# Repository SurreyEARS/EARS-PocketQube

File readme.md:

The SurreyEARS foray into picosatellite development. We are using the new PQ60 V1.1 Standard from  http://pqinfo.info

See the project wiki here: http://wiki.surreyears.co.uk/index.php/EARS_PocketQube_Picosatellite

License
=======

EARS-Pocketqube | http://wiki.surreyears.co.uk/index.php/EARS_PocketQube_Picosatellite
Copyright (c) 2015 SurreyEARS

This is an open hardware design licensed under the terms of the CERN Open
Hardware Licence (OHL) v1.2.

You may redistribute and modify this documentation under the terms of the CERN
OHL v.1.2 (http://ohwr.org/cernohl). This documentation is distributed WITHOUT
ANY EXPRESS OR IMPLIED WARRANTY, INCLUDING OF MERCHANTABILITY, SATISFACTORY
QUALITY AND FITNESS FOR A PARTICULAR PURPOSE. Please see the CERN OHL v.1.2 for
applicable conditions.

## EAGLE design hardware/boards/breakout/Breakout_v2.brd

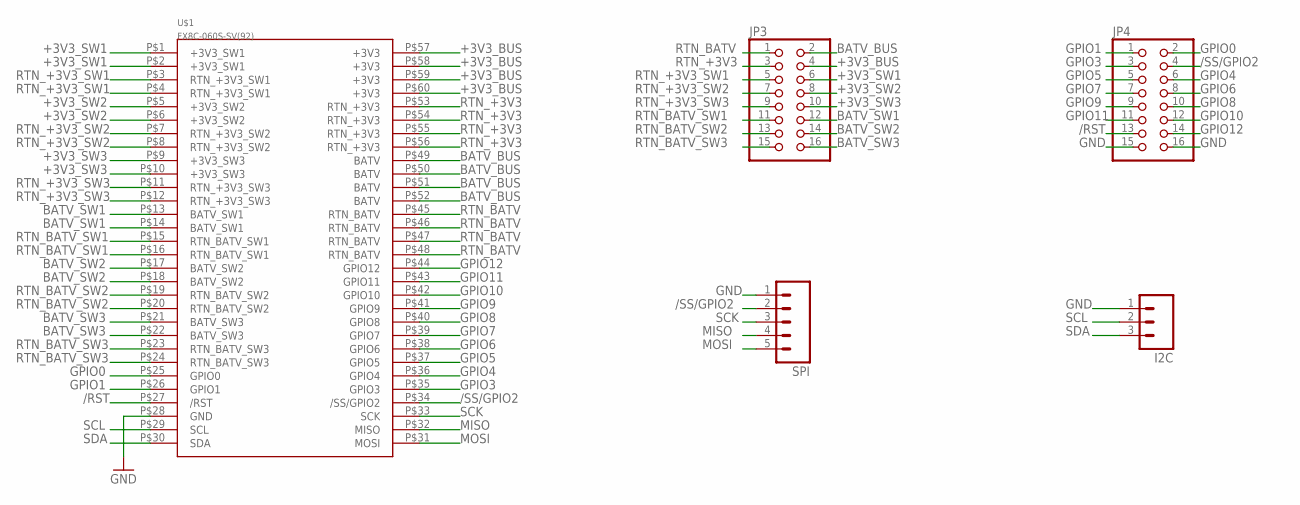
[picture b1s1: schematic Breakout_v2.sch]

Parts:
I2C: M03PTH; 1X03
JP3, JP4: PINHD-2X8; 2X08
SPI: M05PTH; 1X05
U$1: FX8C-060S-SV(92)

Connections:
+3V3_BUS: JP3.4, U$1.P$57 (+3V3), U$1.P$58 (+3V3), U$1.P$59 (+3V3), U$1.P$60 (+3V3)
+3V3_SW1: JP3.6, U$1.P$1 (+3V3_SW1), U$1.P$2 (+3V3_SW1)
+3V3_SW2: JP3.8, U$1.P$5 (+3V3_SW2), U$1.P$6 (+3V3_SW2)
+3V3_SW3: JP3.10, U$1.P$9 (+3V3_SW3), U$1.P$10 (+3V3_SW3)
/RST: JP4.13, U$1.P$27 (/RST)
/SS/GPIO2: JP4.4, SPI.2, U$1.P$34 (/SS/GPIO2)
BATV_BUS: JP3.2, U$1.P$49 (BATV), U$1.P$50 (BATV), U$1.P$51 (BATV), U$1.P$52 (BATV)
BATV_SW1: JP3.12, U$1.P$13 (BATV_SW1), U$1.P$14 (BATV_SW1)
BATV_SW2: JP3.14, U$1.P$17 (BATV_SW2), U$1.P$18 (BATV_SW2)
BATV_SW3: JP3.16, U$1.P$21 (BATV_SW3), U$1.P$22 (BATV_SW3)
GND: I2C.1, JP4.15, JP4.16, SPI.1, U$1.P$28 (GND)
GPIO0: JP4.2, U$1.P$25 (GPIO0)
GPIO1: JP4.1, U$1.P$26 (GPIO1)
GPIO3: JP4.3, U$1.P$35 (GPIO3)
GPIO4: JP4.6, U$1.P$36 (GPIO4)
GPIO5: JP4.5, U$1.P$37 (GPIO5)
GPIO6: JP4.8, U$1.P$38 (GPIO6)
GPIO7: JP4.7, U$1.P$39 (GPIO7)
GPIO8: JP4.10, U$1.P$40 (GPIO8)
GPIO9: JP4.9, U$1.P$41 (GPIO9)
GPIO10: JP4.12, U$1.P$42 (GPIO10)
GPIO11: JP4.11, U$1.P$43 (GPIO11)
GPIO12: JP4.14, U$1.P$44 (GPIO12)
MISO: SPI.4, U$1.P$32 (MISO)
MOSI: SPI.5, U$1.P$31 (MOSI)
RTN_+3V3: JP3.3, U$1.P$53 (RTN_+3V3), U$1.P$54 (RTN_+3V3), U$1.P$55 (RTN_+3V3), U$1.P$56 (RTN_+3V3)
RTN_+3V3_SW1: JP3.5, U$1.P$3 (RTN_+3V3_SW1), U$1.P$4 (RTN_+3V3_SW1)
RTN_+3V3_SW2: JP3.7, U$1.P$7 (RTN_+3V3_SW2), U$1.P$8 (RTN_+3V3_SW2)
RTN_+3V3_SW3: JP3.9, U$1.P$11 (RTN_+3V3_SW3), U$1.P$12 (RTN_+3V3_SW3)
RTN_BATV: JP3.1, U$1.P$45 (RTN_BATV), U$1.P$46 (RTN_BATV), U$1.P$47 (RTN_BATV), U$1.P$48 (RTN_BATV)
RTN_BATV_SW1: JP3.11, U$1.P$15 (RTN_BATV_SW1), U$1.P$16 (RTN_BATV_SW1)
RTN_BATV_SW2: JP3.13, U$1.P$19 (RTN_BATV_SW2), U$1.P$20 (RTN_BATV_SW2)
RTN_BATV_SW3: JP3.15, U$1.P$23 (RTN_BATV_SW3), U$1.P$24 (RTN_BATV_SW3)
SCK: SPI.3, U$1.P$33 (SCK)
SCL: I2C.2, U$1.P$29 (SCL)
SDA: I2C.3, U$1.P$30 (SDA)

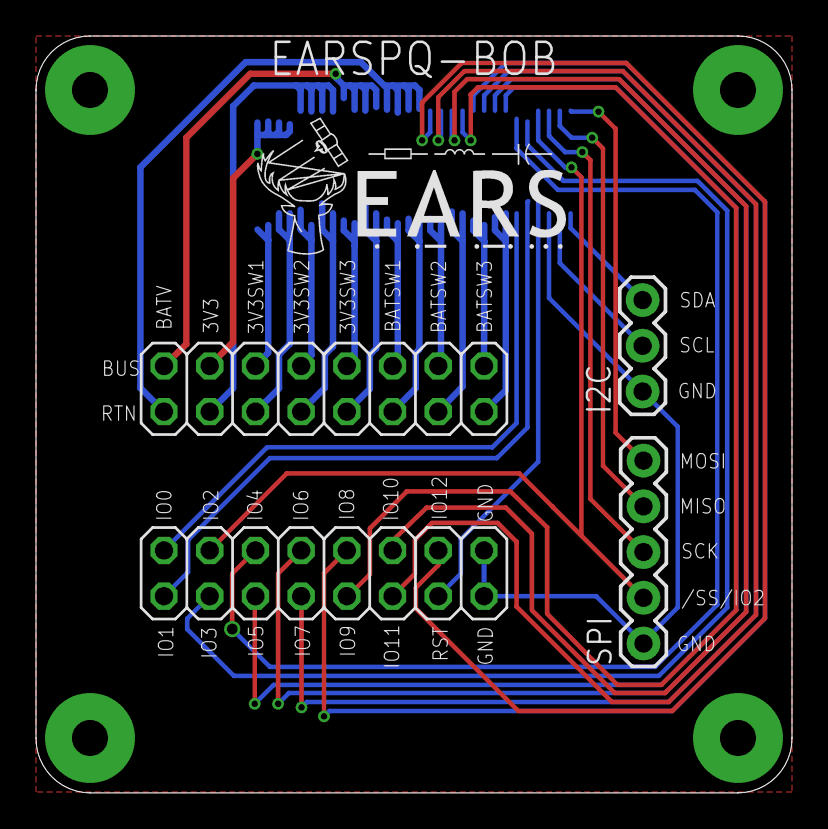
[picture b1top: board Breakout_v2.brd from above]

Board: 2 copper layers, 42.0 x 42.0 mm, 6 parts (1 on the bottom side), 36 nets.

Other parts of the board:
U$2: EARSLOGOFULL

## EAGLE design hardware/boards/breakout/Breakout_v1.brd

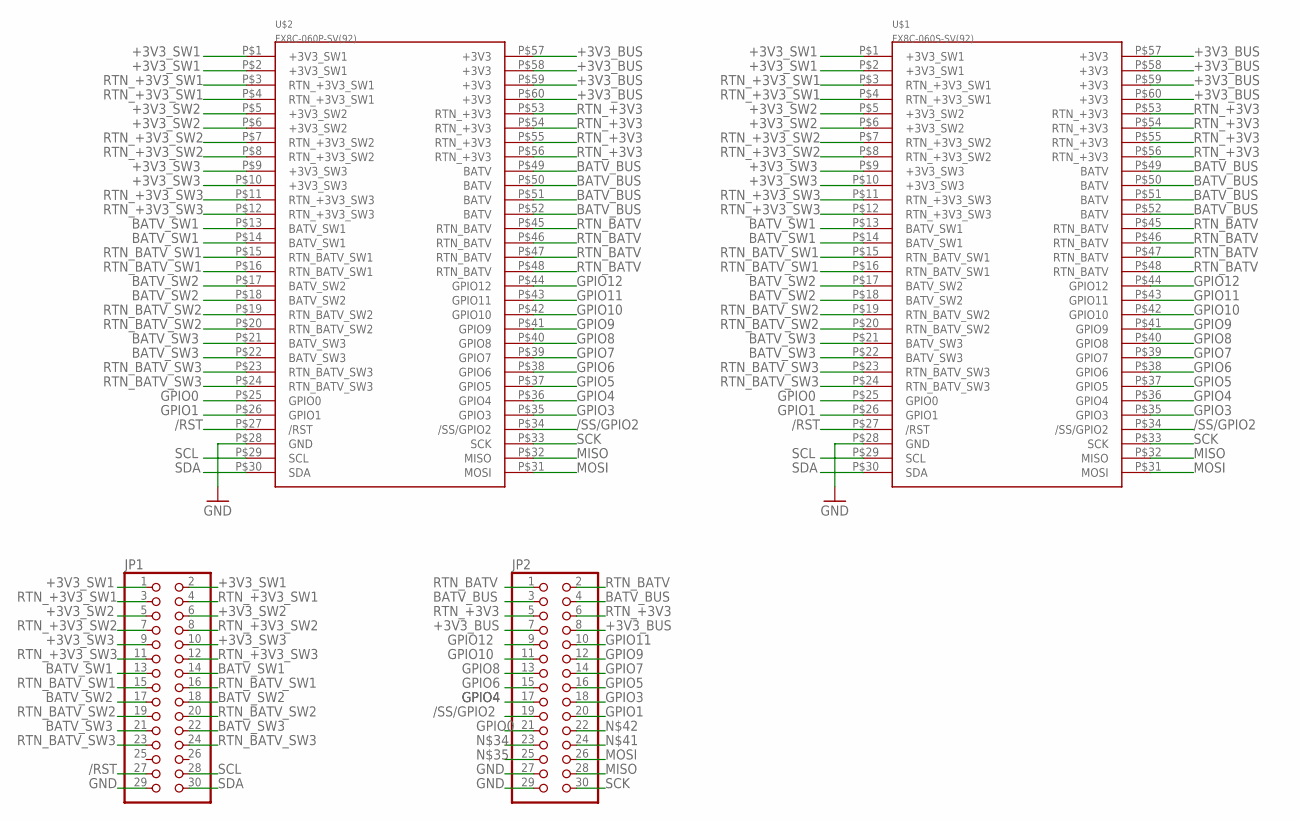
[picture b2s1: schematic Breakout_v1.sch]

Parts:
JP1, JP2: PINHD-2X15; 2X15
U$1: FX8C-060S-SV(92)
U$2: FX8C-060P-SV(92)

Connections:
+3V3_BUS: JP2.7, JP2.8, U$1.P$57 (+3V3), U$1.P$58 (+3V3), U$1.P$59 (+3V3), U$1.P$60 (+3V3), U$2.P$57 (+3V3), U$2.P$58 (+3V3), U$2.P$59 (+3V3), U$2.P$60 (+3V3)
+3V3_SW1: JP1.1, JP1.2, U$1.P$1 (+3V3_SW1), U$1.P$2 (+3V3_SW1), U$2.P$1 (+3V3_SW1), U$2.P$2 (+3V3_SW1)
+3V3_SW2: JP1.5, JP1.6, U$1.P$5 (+3V3_SW2), U$1.P$6 (+3V3_SW2), U$2.P$5 (+3V3_SW2), U$2.P$6 (+3V3_SW2)
+3V3_SW3: JP1.9, JP1.10, U$1.P$9 (+3V3_SW3), U$1.P$10 (+3V3_SW3), U$2.P$9 (+3V3_SW3), U$2.P$10 (+3V3_SW3)
/RST: JP1.27, U$1.P$27 (/RST), U$2.P$27 (/RST)
/SS/GPIO2: JP2.19, U$1.P$34 (/SS/GPIO2), U$2.P$34 (/SS/GPIO2)
BATV_BUS: JP2.3, JP2.4, U$1.P$49 (BATV), U$1.P$50 (BATV), U$1.P$51 (BATV), U$1.P$52 (BATV), U$2.P$49 (BATV), U$2.P$50 (BATV), U$2.P$51 (BATV), U$2.P$52 (BATV)
BATV_SW1: JP1.13, JP1.14, U$1.P$13 (BATV_SW1), U$1.P$14 (BATV_SW1), U$2.P$13 (BATV_SW1), U$2.P$14 (BATV_SW1)
BATV_SW2: JP1.17, JP1.18, U$1.P$17 (BATV_SW2), U$1.P$18 (BATV_SW2), U$2.P$17 (BATV_SW2), U$2.P$18 (BATV_SW2)
BATV_SW3: JP1.21, JP1.22, U$1.P$21 (BATV_SW3), U$1.P$22 (BATV_SW3), U$2.P$21 (BATV_SW3), U$2.P$22 (BATV_SW3)
GND: JP1.29, JP2.27, JP2.29, U$1.P$28 (GND), U$2.P$28 (GND)
GPIO0: JP2.21, U$1.P$25 (GPIO0), U$2.P$25 (GPIO0)
GPIO1: JP2.20, U$1.P$26 (GPIO1), U$2.P$26 (GPIO1)
GPIO3: JP2.18, U$1.P$35 (GPIO3), U$2.P$35 (GPIO3)
GPIO4: JP2.17, U$1.P$36 (GPIO4), U$2.P$36 (GPIO4)
GPIO5: JP2.16, U$1.P$37 (GPIO5), U$2.P$37 (GPIO5)
GPIO6: JP2.15, U$1.P$38 (GPIO6), U$2.P$38 (GPIO6)
GPIO7: JP2.14, U$1.P$39 (GPIO7), U$2.P$39 (GPIO7)
GPIO8: JP2.13, U$1.P$40 (GPIO8), U$2.P$40 (GPIO8)
GPIO9: JP2.12, U$1.P$41 (GPIO9), U$2.P$41 (GPIO9)
GPIO10: JP2.11, U$1.P$42 (GPIO10), U$2.P$42 (GPIO10)
GPIO11: JP2.10, U$1.P$43 (GPIO11), U$2.P$43 (GPIO11)
GPIO12: JP2.9, U$1.P$44 (GPIO12), U$2.P$44 (GPIO12)
MISO: JP2.28, U$1.P$32 (MISO), U$2.P$32 (MISO)
MOSI: JP2.26, U$1.P$31 (MOSI), U$2.P$31 (MOSI)
RTN_+3V3: JP2.5, JP2.6, U$1.P$53 (RTN_+3V3), U$1.P$54 (RTN_+3V3), U$1.P$55 (RTN_+3V3), U$1.P$56 (RTN_+3V3), U$2.P$53 (RTN_+3V3), U$2.P$54 (RTN_+3V3), U$2.P$55 (RTN_+3V3), U$2.P$56 (RTN_+3V3)
RTN_+3V3_SW1: JP1.3, JP1.4, U$1.P$3 (RTN_+3V3_SW1), U$1.P$4 (RTN_+3V3_SW1), U$2.P$3 (RTN_+3V3_SW1), U$2.P$4 (RTN_+3V3_SW1)
RTN_+3V3_SW2: JP1.7, JP1.8, U$1.P$7 (RTN_+3V3_SW2), U$1.P$8 (RTN_+3V3_SW2), U$2.P$7 (RTN_+3V3_SW2), U$2.P$8 (RTN_+3V3_SW2)
RTN_+3V3_SW3: JP1.11, JP1.12, U$1.P$11 (RTN_+3V3_SW3), U$1.P$12 (RTN_+3V3_SW3), U$2.P$11 (RTN_+3V3_SW3), U$2.P$12 (RTN_+3V3_SW3)
RTN_BATV: JP2.1, JP2.2, U$1.P$45 (RTN_BATV), U$1.P$46 (RTN_BATV), U$1.P$47 (RTN_BATV), U$1.P$48 (RTN_BATV), U$2.P$45 (RTN_BATV), U$2.P$46 (RTN_BATV), U$2.P$47 (RTN_BATV), U$2.P$48 (RTN_BATV)
RTN_BATV_SW1: JP1.15, JP1.16, U$1.P$15 (RTN_BATV_SW1), U$1.P$16 (RTN_BATV_SW1), U$2.P$15 (RTN_BATV_SW1), U$2.P$16 (RTN_BATV_SW1)
RTN_BATV_SW2: JP1.19, JP1.20, U$1.P$19 (RTN_BATV_SW2), U$1.P$20 (RTN_BATV_SW2), U$2.P$19 (RTN_BATV_SW2), U$2.P$20 (RTN_BATV_SW2)
RTN_BATV_SW3: JP1.23, JP1.24, U$1.P$23 (RTN_BATV_SW3), U$1.P$24 (RTN_BATV_SW3), U$2.P$23 (RTN_BATV_SW3), U$2.P$24 (RTN_BATV_SW3)
SCK: JP2.30, U$1.P$33 (SCK), U$2.P$33 (SCK)
SCL: JP1.28, U$1.P$29 (SCL), U$2.P$29 (SCL)
SDA: JP1.30, U$1.P$30 (SDA), U$2.P$30 (SDA)

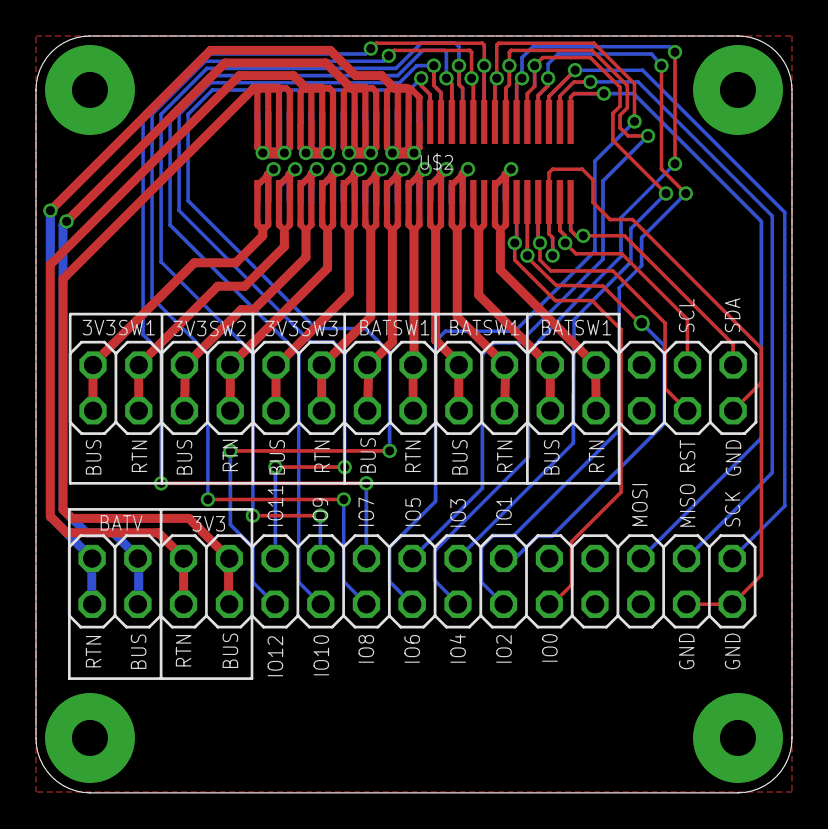
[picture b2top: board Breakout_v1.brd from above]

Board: 2 copper layers, 42.0 x 42.0 mm, 4 parts (1 on the bottom side), 36 nets.

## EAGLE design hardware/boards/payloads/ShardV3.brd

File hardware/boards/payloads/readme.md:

This folder will contain designs for payload boards. Current ideas include:

* Camera
* Radiation Detection
* Prototyping

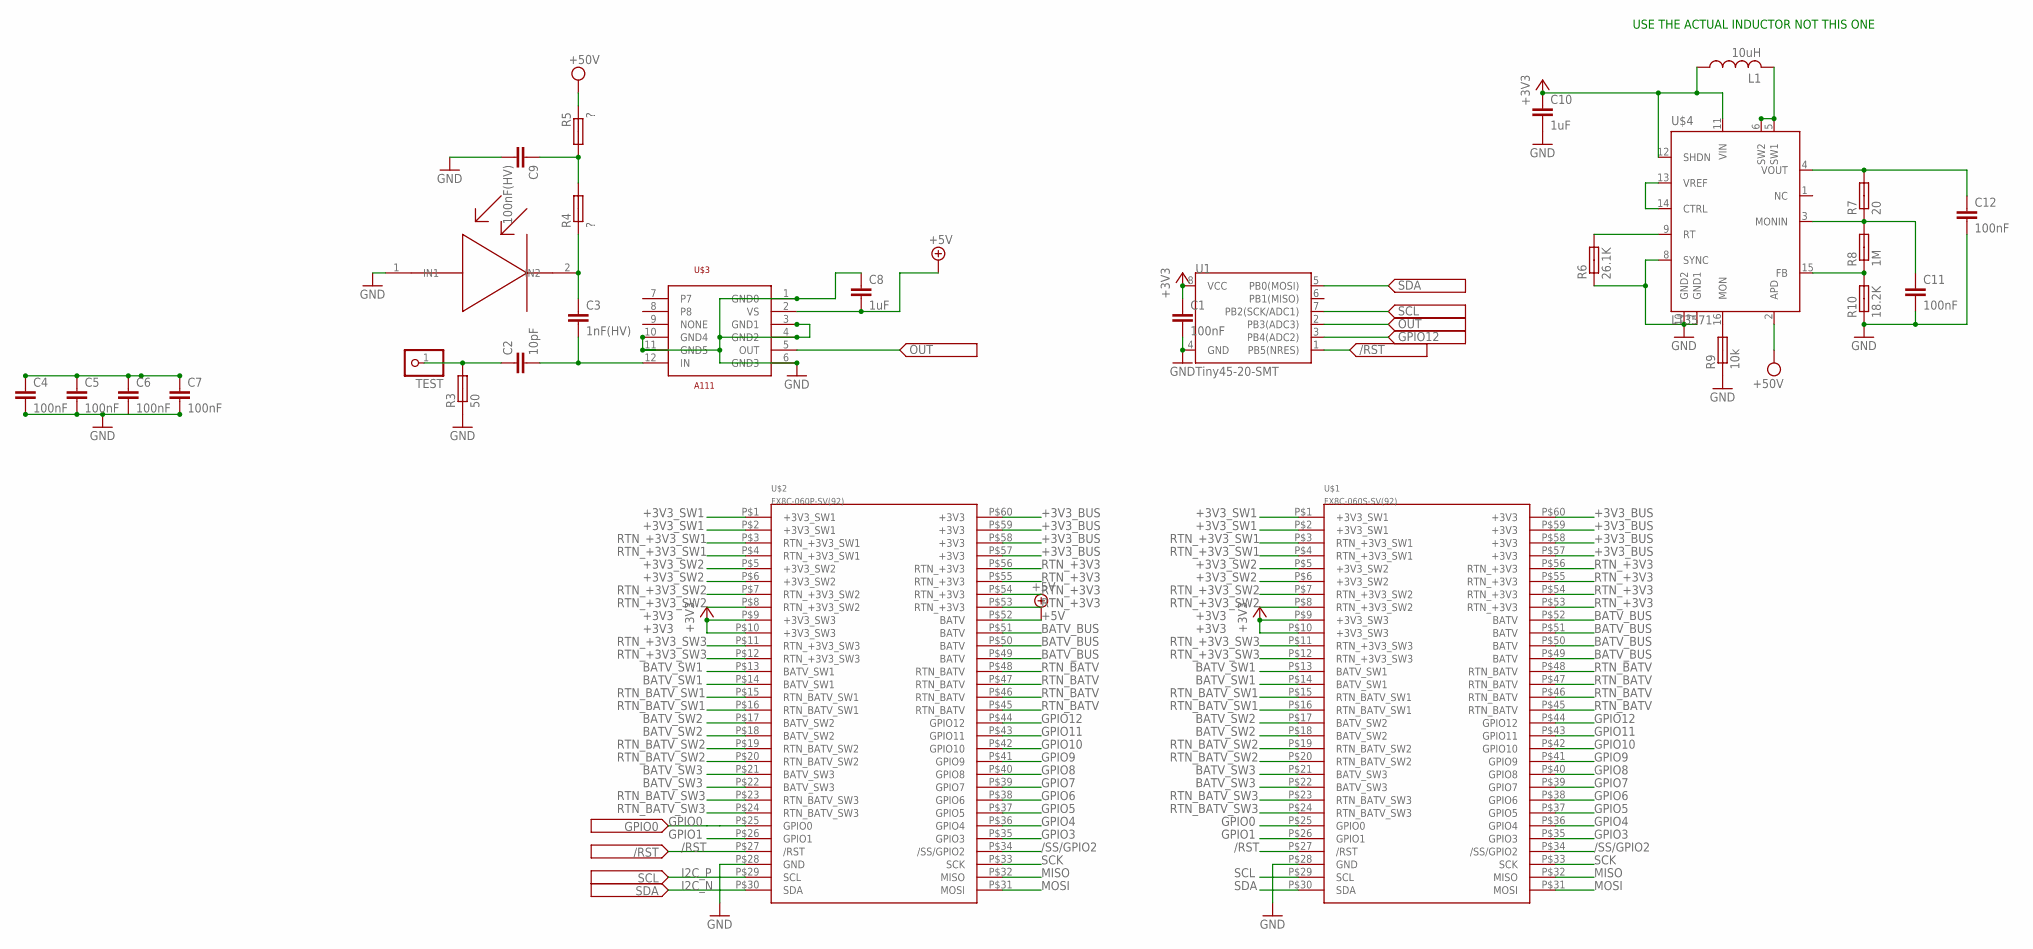
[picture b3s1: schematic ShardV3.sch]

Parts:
C1, C4, C5, C6, C7: 100nF; C0402
C2: 10pF; C0402
C3: 1nF(HV); C0603
C8, C10: 1uF; C0603
C9: 100nF(HV); C0603
C11, C12: 100nF; C0603
L1: 10uH; L1812
NDD: S3590-08
R3: 50; R0402
R4, R5: ?; R0402
R6: 26.1K; R0402
R7: 20; R0402
R8: 1M; R0402
R9: 10k; R0402
R10: 18.2K; R0402
TEST: PINHD-1X1; 1X01
U1: Tiny45-20-SMT; SO08-EIAJ
U$1: FX8C-060S-SV(92)
U$2: FX8C-060P-SV(92)
U$3: A111CHIP
U$4: LT3571; QFN3X3-6

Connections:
+3V3: C1.1, C10.1, L1.1, U1.8 (VCC), U$1.P$9 (+3V3_SW3), U$1.P$10 (+3V3_SW3), U$2.P$9 (+3V3_SW3), U$2.P$10 (+3V3_SW3), U$4.11 (VIN), U$4.12 (SHDN)
+3V3_BUS: U$1.P$57 (+3V3), U$1.P$58 (+3V3), U$1.P$59 (+3V3), U$1.P$60 (+3V3), U$2.P$57 (+3V3), U$2.P$58 (+3V3), U$2.P$59 (+3V3), U$2.P$60 (+3V3)
+3V3_SW1: U$1.P$1 (+3V3_SW1), U$1.P$2 (+3V3_SW1), U$2.P$1 (+3V3_SW1), U$2.P$2 (+3V3_SW1)
+3V3_SW2: U$1.P$5 (+3V3_SW2), U$1.P$6 (+3V3_SW2), U$2.P$5 (+3V3_SW2), U$2.P$6 (+3V3_SW2)
+5V: C8.2, U$2.P$52 (BATV), U$3.2 (VS)
/RST: U1.1 (PB5(NRES)), U$1.P$27 (/RST), U$2.P$27 (/RST)
/SS/GPIO2: U$1.P$34 (/SS/GPIO2), U$2.P$34 (/SS/GPIO2)
BATV_BUS: U$1.P$49 (BATV), U$1.P$50 (BATV), U$1.P$51 (BATV), U$1.P$52 (BATV), U$2.P$49 (BATV), U$2.P$50 (BATV), U$2.P$51 (BATV)
BATV_SW1: U$1.P$13 (BATV_SW1), U$1.P$14 (BATV_SW1), U$2.P$13 (BATV_SW1), U$2.P$14 (BATV_SW1)
BATV_SW2: U$1.P$17 (BATV_SW2), U$1.P$18 (BATV_SW2), U$2.P$17 (BATV_SW2), U$2.P$18 (BATV_SW2)
BATV_SW3: U$1.P$21 (BATV_SW3), U$1.P$22 (BATV_SW3), U$2.P$21 (BATV_SW3), U$2.P$22 (BATV_SW3)
CHASSIS_GND: C4.1, C5.1, C6.1, C7.1
GND: C1.2, C4.2, C5.2, C7.2, C8.1, C9.2, C10.2, C11.2, C12.2, NDD.1 (IN1), R3.1, R6.1, R9.1, R10.1, U1.4 (GND), U$1.P$28 (GND), U$2.P$28 (GND), U$3.1 (GND0), U$3.3 (GND1), U$3.4 (GND2), U$3.6 (GND3), U$3.10 (GND4), U$3.11 (GND5), U$4.7 (GND1), U$4.8 (SYNC), U$4.10 (GND2)
GPIO0: U$1.P$25 (GPIO0), U$2.P$25 (GPIO0)
GPIO1: U$1.P$26 (GPIO1), U$2.P$26 (GPIO1)
GPIO3: U$1.P$35 (GPIO3), U$2.P$35 (GPIO3)
GPIO4: U$1.P$36 (GPIO4), U$2.P$36 (GPIO4)
GPIO5: U$1.P$37 (GPIO5), U$2.P$37 (GPIO5)
GPIO6: U$1.P$38 (GPIO6), U$2.P$38 (GPIO6)
GPIO7: U$1.P$39 (GPIO7), U$2.P$39 (GPIO7)
GPIO8: U$1.P$40 (GPIO8), U$2.P$40 (GPIO8)
GPIO9: U$1.P$41 (GPIO9), U$2.P$41 (GPIO9)
GPIO10: U$1.P$42 (GPIO10), U$2.P$42 (GPIO10)
GPIO11: U$1.P$43 (GPIO11), U$2.P$43 (GPIO11)
GPIO12: U1.3 (PB4(ADC2)), U$1.P$44 (GPIO12), U$2.P$44 (GPIO12)
I2C_N: U1.5 (PB0(MOSI)), U$2.P$30 (SDA)
I2C_P: U1.7 (PB2(SCK/ADC1)), U$2.P$29 (SCL)
MISO: U$1.P$32 (MISO), U$2.P$32 (MISO)
MOSI: U$1.P$31 (MOSI), U$2.P$31 (MOSI)
unnamed: C2.1, R3.2, TEST.1
unnamed: C2.2, C3.2, U$3.12 (IN)
unnamed: C3.1, NDD.2 (IN2), R4.1
unnamed: L1.2, U$4.5 (SW1), U$4.6 (SW2)
unnamed: C9.1, R4.2, R5.2
unnamed: U$4.13 (VREF), U$4.14 (CTRL)
unnamed: R6.2, U$4.9 (RT)
unnamed: C11.1, R7.1, R8.2, U$4.3 (MONIN)
unnamed: C12.1, R7.2, U$4.4 (VOUT)
unnamed: R8.1, R10.2, U$4.15 (FB)
unnamed: R9.2, U$4.16 (MON)
OUT: U1.2 (PB3(ADC3)), U$3.5 (OUT)
RTN_+3V3: U$1.P$53 (RTN_+3V3), U$1.P$54 (RTN_+3V3), U$1.P$55 (RTN_+3V3), U$1.P$56 (RTN_+3V3), U$2.P$53 (RTN_+3V3), U$2.P$54 (RTN_+3V3), U$2.P$55 (RTN_+3V3), U$2.P$56 (RTN_+3V3)
RTN_+3V3_SW1: U$1.P$3 (RTN_+3V3_SW1), U$1.P$4 (RTN_+3V3_SW1), U$2.P$3 (RTN_+3V3_SW1), U$2.P$4 (RTN_+3V3_SW1)
RTN_+3V3_SW2: U$1.P$7 (RTN_+3V3_SW2), U$1.P$8 (RTN_+3V3_SW2), U$2.P$7 (RTN_+3V3_SW2), U$2.P$8 (RTN_+3V3_SW2)
RTN_+3V3_SW3: U$1.P$11 (RTN_+3V3_SW3), U$1.P$12 (RTN_+3V3_SW3), U$2.P$11 (RTN_+3V3_SW3), U$2.P$12 (RTN_+3V3_SW3)
RTN_BATV: U$1.P$45 (RTN_BATV), U$1.P$46 (RTN_BATV), U$1.P$47 (RTN_BATV), U$1.P$48 (RTN_BATV), U$2.P$45 (RTN_BATV), U$2.P$46 (RTN_BATV), U$2.P$47 (RTN_BATV), U$2.P$48 (RTN_BATV)
RTN_BATV_SW1: U$1.P$15 (RTN_BATV_SW1), U$1.P$16 (RTN_BATV_SW1), U$2.P$15 (RTN_BATV_SW1), U$2.P$16 (RTN_BATV_SW1)
RTN_BATV_SW2: U$1.P$19 (RTN_BATV_SW2), U$1.P$20 (RTN_BATV_SW2), U$2.P$19 (RTN_BATV_SW2), U$2.P$20 (RTN_BATV_SW2)
RTN_BATV_SW3: U$1.P$23 (RTN_BATV_SW3), U$1.P$24 (RTN_BATV_SW3), U$2.P$23 (RTN_BATV_SW3), U$2.P$24 (RTN_BATV_SW3)
SCK: U$1.P$33 (SCK), U$2.P$33 (SCK)
SCL: U$1.P$29 (SCL)
SDA: U$1.P$30 (SDA)
VPP: R5.1, U$4.2 (APD)

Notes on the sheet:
USE THE ACTUAL INDUCTOR NOT THIS ONE

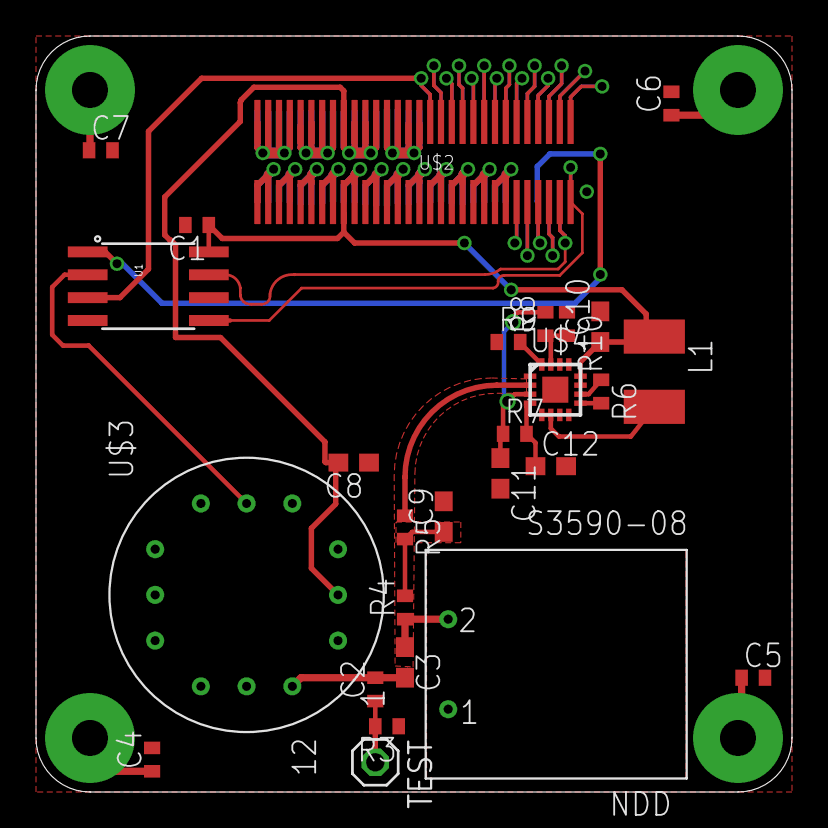
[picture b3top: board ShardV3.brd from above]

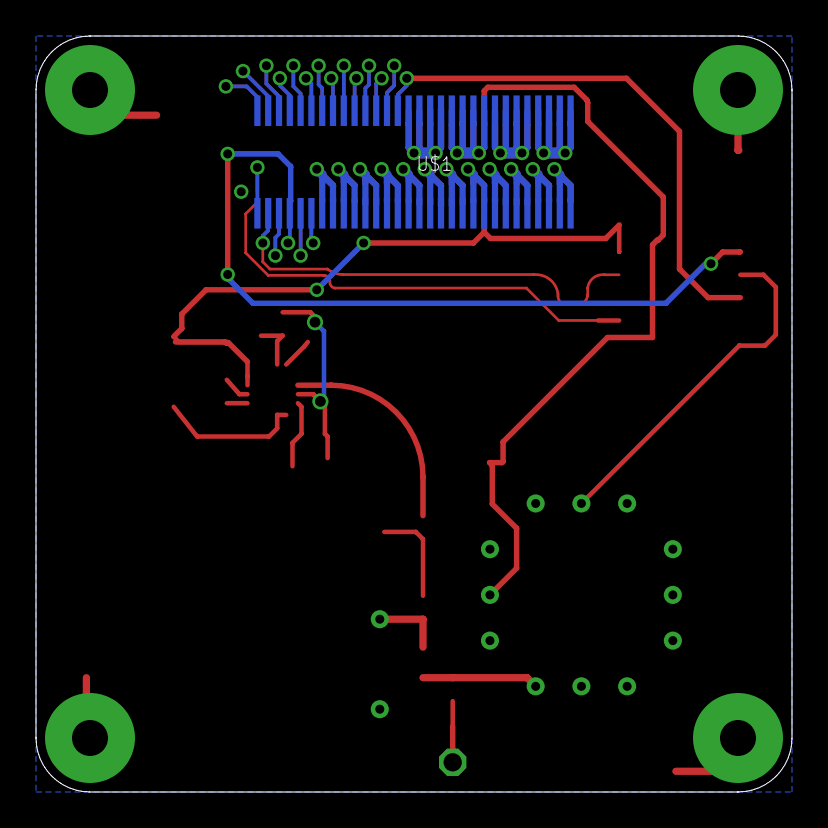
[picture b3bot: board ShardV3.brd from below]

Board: 2 copper layers, 42.0 x 42.0 mm, 29 parts (2 on the bottom side), 51 nets.

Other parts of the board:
U$5: EARSLOGOFULL

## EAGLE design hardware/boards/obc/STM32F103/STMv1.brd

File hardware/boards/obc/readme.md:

We are intending to roll out several obc boards which contain different processors.

Current ideas include:
* ATMega328P
* Teensy (ARM Cortex M4)
* STM Nucleo
* TI MSP430
* Freescale Kinetis L
* Intel Edison(!)

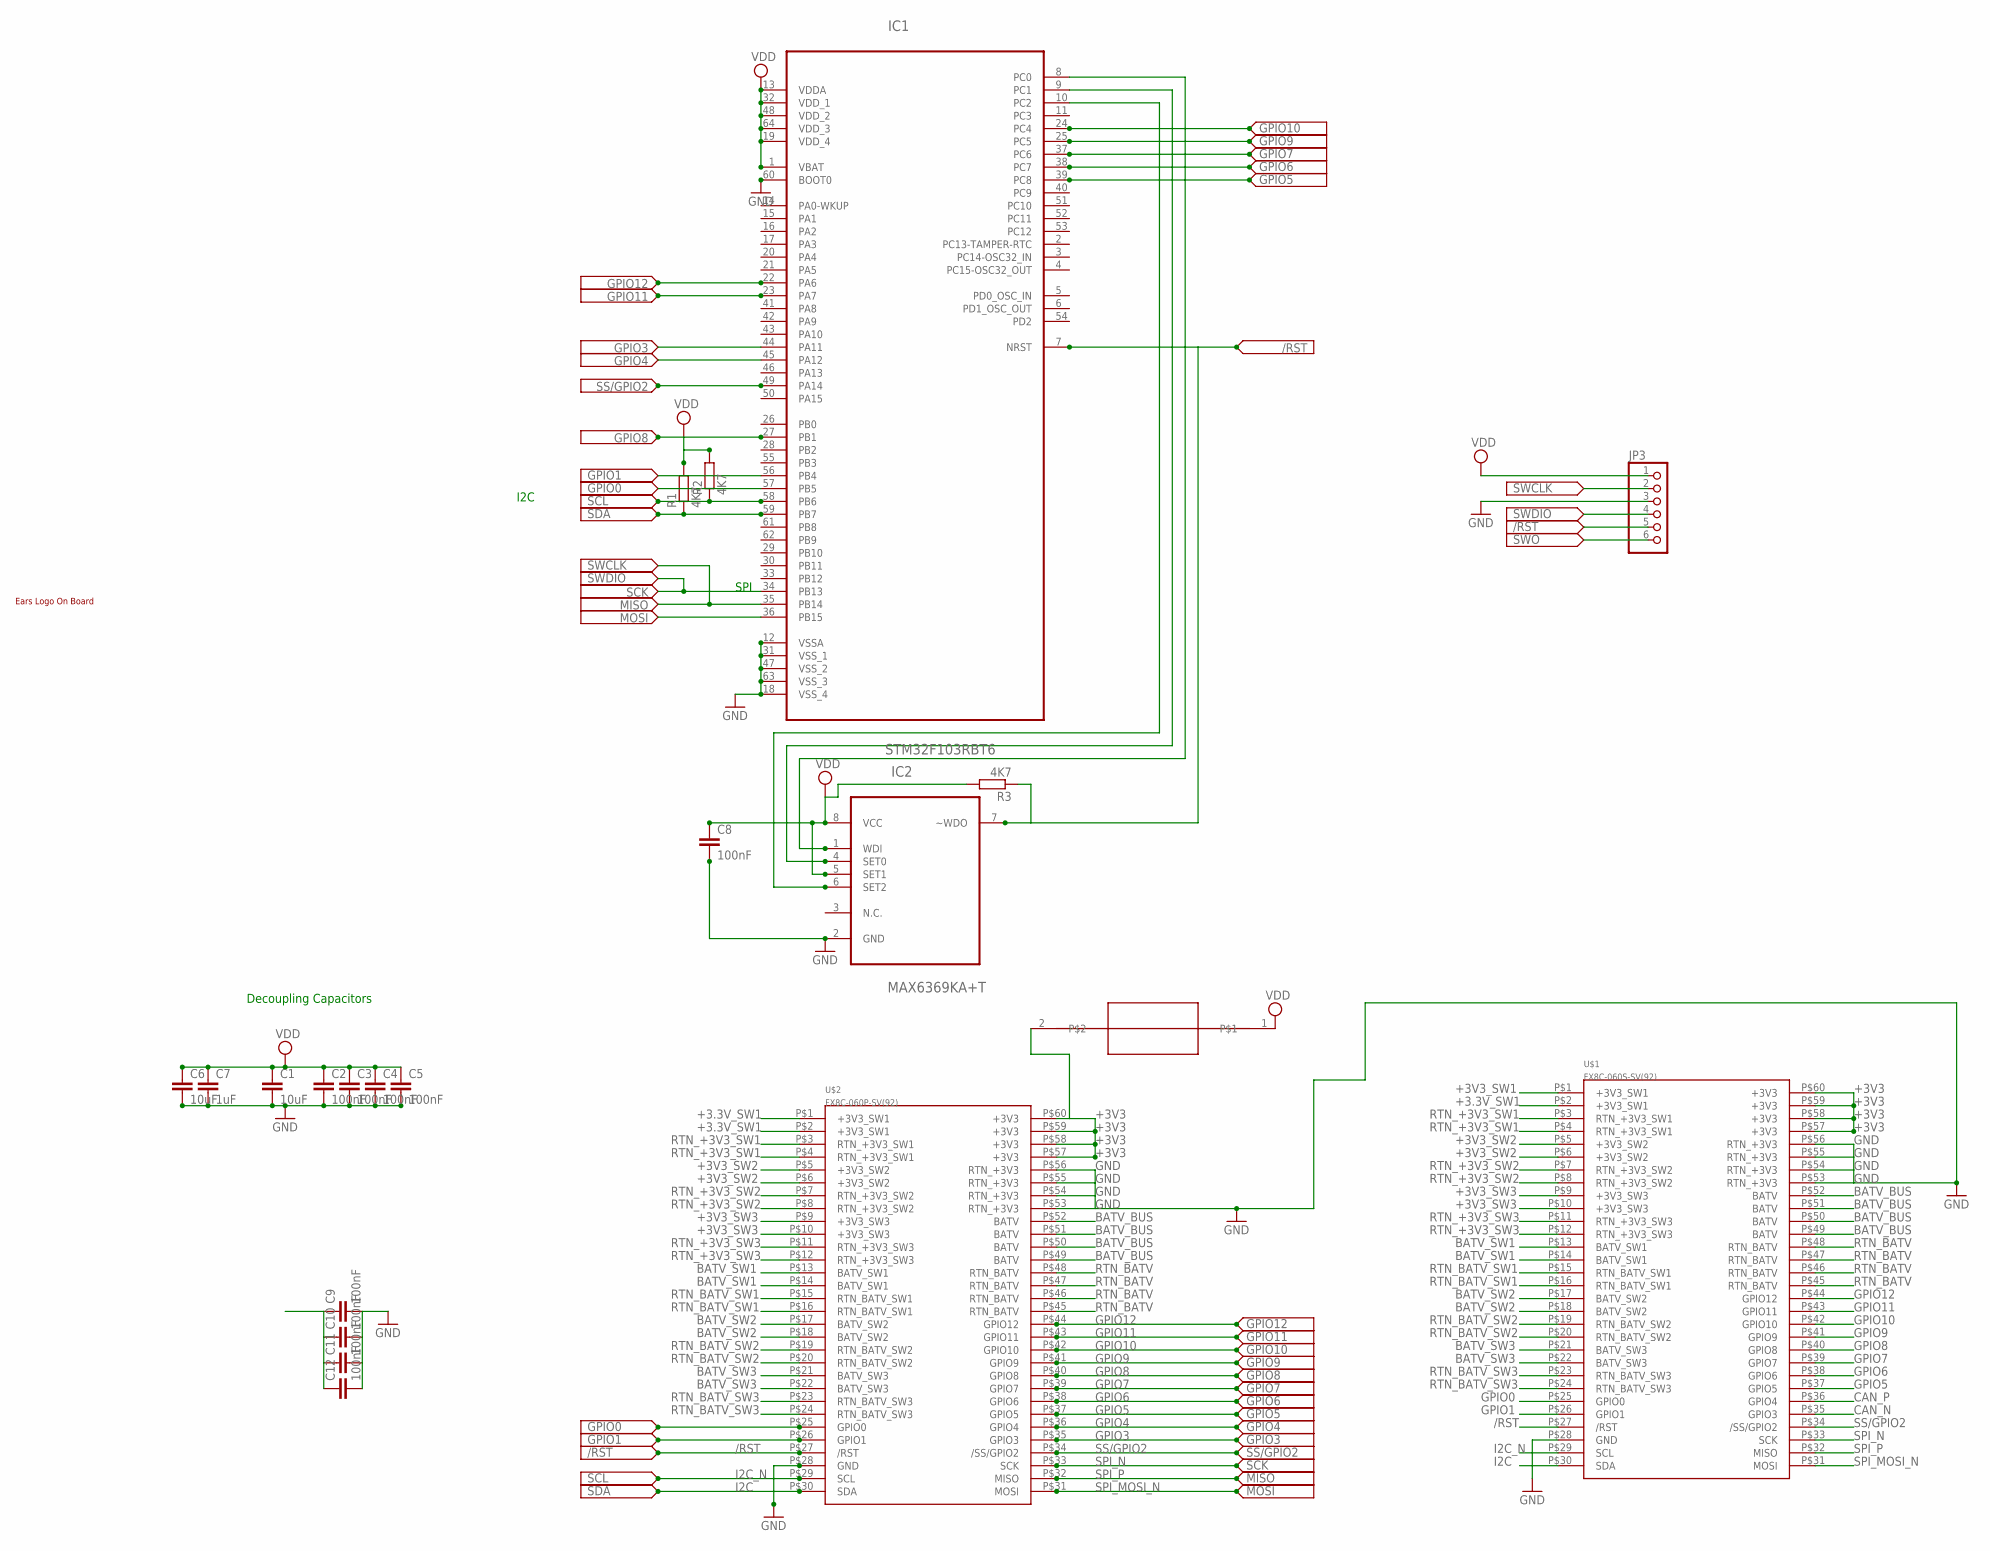
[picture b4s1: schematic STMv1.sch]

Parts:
C1, C6: 10uF; C0603
C2, C3, C4, C5, C8, C9, C10, C11, C12: 100nF; C0603
C7: 1uF; C0603
FUSE: 0603POLYFUSE; R0603
IC1: STM32F103RBT6; QFP50P1200X1200X160-64N
IC2: MAX6369KA+T; SOT65P280X145-8N
JP3: PINHD-1X6; 1X06
R1, R2, R3: 4K7; R0603
U$1: FX8C-060S-SV(92)
U$2: FX8C-060P-SV(92)
U$3: EARSLOGOFULL

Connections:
+3.3V_SW1: U$1.P$2 (+3V3_SW1), U$2.P$1 (+3V3_SW1), U$2.P$2 (+3V3_SW1)
+3V3: FUSE.2, U$1.P$57 (+3V3), U$1.P$58 (+3V3), U$1.P$59 (+3V3), U$1.P$60 (+3V3), U$2.P$57 (+3V3), U$2.P$58 (+3V3), U$2.P$59 (+3V3), U$2.P$60 (+3V3)
+3V3_SW1: U$1.P$1 (+3V3_SW1)
+3V3_SW2: U$1.P$5 (+3V3_SW2), U$1.P$6 (+3V3_SW2), U$2.P$5 (+3V3_SW2), U$2.P$6 (+3V3_SW2)
+3V3_SW3: U$1.P$9 (+3V3_SW3), U$1.P$10 (+3V3_SW3), U$2.P$9 (+3V3_SW3), U$2.P$10 (+3V3_SW3)
/RST: IC1.7 (NRST), IC2.7 (~WDO), R3.1, U$1.P$27 (/RST), U$2.P$27 (/RST)
BATV_BUS: U$1.P$49 (BATV), U$1.P$50 (BATV), U$1.P$51 (BATV), U$1.P$52 (BATV), U$2.P$49 (BATV), U$2.P$50 (BATV), U$2.P$51 (BATV), U$2.P$52 (BATV)
BATV_SW1: U$1.P$13 (BATV_SW1), U$1.P$14 (BATV_SW1), U$2.P$13 (BATV_SW1), U$2.P$14 (BATV_SW1)
BATV_SW2: U$1.P$17 (BATV_SW2), U$1.P$18 (BATV_SW2), U$2.P$17 (BATV_SW2), U$2.P$18 (BATV_SW2)
BATV_SW3: U$1.P$21 (BATV_SW3), U$1.P$22 (BATV_SW3), U$2.P$21 (BATV_SW3), U$2.P$22 (BATV_SW3)
CAN_N: U$1.P$35 (GPIO3)
CAN_P: U$1.P$36 (GPIO4)
CHASSIS_GND: C9.1, C10.1, C11.1, C12.1
GND: C1.2, C2.2, C3.2, C4.2, C5.2, C6.2, C7.2, C8.2, C9.2, C10.2, C11.2, C12.2, IC1.12 (VSSA), IC1.18 (VSS_4), IC1.31 (VSS_1), IC1.47 (VSS_2), IC1.60 (BOOT0), IC1.63 (VSS_3), IC2.2 (GND), JP3.3 (GND), U$1.P$28 (GND), U$1.P$53 (RTN_+3V3), U$1.P$54 (RTN_+3V3), U$1.P$55 (RTN_+3V3), U$1.P$56 (RTN_+3V3), U$2.P$28 (GND), U$2.P$53 (RTN_+3V3), U$2.P$54 (RTN_+3V3), U$2.P$55 (RTN_+3V3), U$2.P$56 (RTN_+3V3)
GPIO0: IC1.57 (PB5), U$1.P$25 (GPIO0), U$2.P$25 (GPIO0)
GPIO1: IC1.56 (PB4), U$1.P$26 (GPIO1), U$2.P$26 (GPIO1)
GPIO3: IC1.44 (PA11), U$2.P$35 (GPIO3)
GPIO4: IC1.45 (PA12), U$2.P$36 (GPIO4)
GPIO5: IC1.39 (PC8), U$1.P$37 (GPIO5), U$2.P$37 (GPIO5)
GPIO6: IC1.38 (PC7), U$1.P$38 (GPIO6), U$2.P$38 (GPIO6)
GPIO7: IC1.37 (PC6), U$1.P$39 (GPIO7), U$2.P$39 (GPIO7)
GPIO8: IC1.27 (PB1), U$1.P$40 (GPIO8), U$2.P$40 (GPIO8)
GPIO9: IC1.25 (PC5), U$1.P$41 (GPIO9), U$2.P$41 (GPIO9)
GPIO10: IC1.24 (PC4), U$1.P$42 (GPIO10), U$2.P$42 (GPIO10)
GPIO11: IC1.23 (PA7), U$1.P$43 (GPIO11), U$2.P$43 (GPIO11)
GPIO12: IC1.22 (PA6), U$1.P$44 (GPIO12), U$2.P$44 (GPIO12)
I2C: IC1.59 (PB7), R1.1, U$1.P$30 (SDA), U$2.P$30 (SDA)
I2C_N: IC1.58 (PB6), R2.1, U$1.P$29 (SCL), U$2.P$29 (SCL)
RTN_+3V3_SW1: U$1.P$3 (RTN_+3V3_SW1), U$1.P$4 (RTN_+3V3_SW1), U$2.P$3 (RTN_+3V3_SW1), U$2.P$4 (RTN_+3V3_SW1)
RTN_+3V3_SW2: U$1.P$7 (RTN_+3V3_SW2), U$1.P$8 (RTN_+3V3_SW2), U$2.P$7 (RTN_+3V3_SW2), U$2.P$8 (RTN_+3V3_SW2)
RTN_+3V3_SW3: U$1.P$11 (RTN_+3V3_SW3), U$1.P$12 (RTN_+3V3_SW3), U$2.P$11 (RTN_+3V3_SW3), U$2.P$12 (RTN_+3V3_SW3)
RTN_BATV: U$1.P$45 (RTN_BATV), U$1.P$46 (RTN_BATV), U$1.P$47 (RTN_BATV), U$1.P$48 (RTN_BATV), U$2.P$45 (RTN_BATV), U$2.P$46 (RTN_BATV), U$2.P$47 (RTN_BATV), U$2.P$48 (RTN_BATV)
RTN_BATV_SW1: U$1.P$15 (RTN_BATV_SW1), U$1.P$16 (RTN_BATV_SW1), U$2.P$15 (RTN_BATV_SW1), U$2.P$16 (RTN_BATV_SW1)
RTN_BATV_SW2: U$1.P$19 (RTN_BATV_SW2), U$1.P$20 (RTN_BATV_SW2), U$2.P$19 (RTN_BATV_SW2), U$2.P$20 (RTN_BATV_SW2)
RTN_BATV_SW3: U$1.P$23 (RTN_BATV_SW3), U$1.P$24 (RTN_BATV_SW3), U$2.P$23 (RTN_BATV_SW3), U$2.P$24 (RTN_BATV_SW3)
SET0: IC1.9 (PC1), IC2.4 (SET0)
SET2: IC1.10 (PC2), IC2.6 (SET2)
SPI_MOSI_N: IC1.36 (PB15), U$1.P$31 (MOSI), U$2.P$31 (MOSI)
SPI_N: IC1.34 (PB13), JP3.4 (SWDIO), U$1.P$33 (SCK), U$2.P$33 (SCK)
SPI_P: IC1.35 (PB14), JP3.2 (SWCLK), U$1.P$32 (MISO), U$2.P$32 (MISO)
SS/GPIO2: IC1.49 (PA14), U$1.P$34 (/SS/GPIO2), U$2.P$34 (/SS/GPIO2)
VDD: C1.1, C2.1, C3.1, C4.1, C5.1, C6.1, C7.1, C8.1, FUSE.1, IC1.1 (VBAT), IC1.13 (VDDA), IC1.19 (VDD_4), IC1.32 (VDD_1), IC1.48 (VDD_2), IC1.64 (VDD_3), IC2.5 (SET1), IC2.8 (VCC), JP3.1 (VDD), R1.2, R2.2, R3.2
WDI: IC1.8 (PC0), IC2.1 (WDI)

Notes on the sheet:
Decoupling Capacitors
I2C
SPI

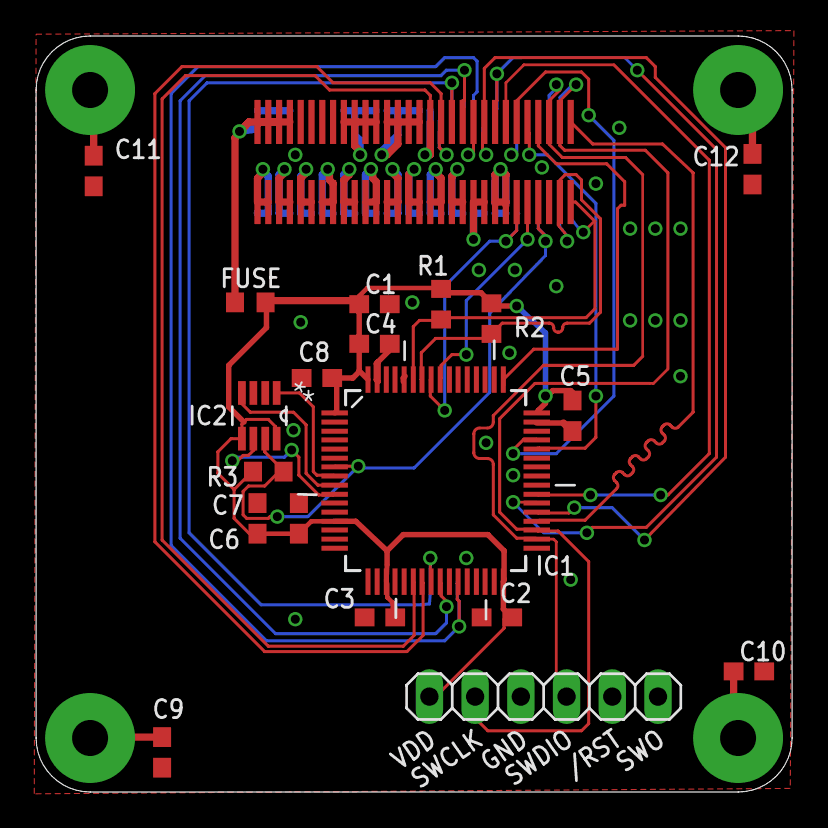
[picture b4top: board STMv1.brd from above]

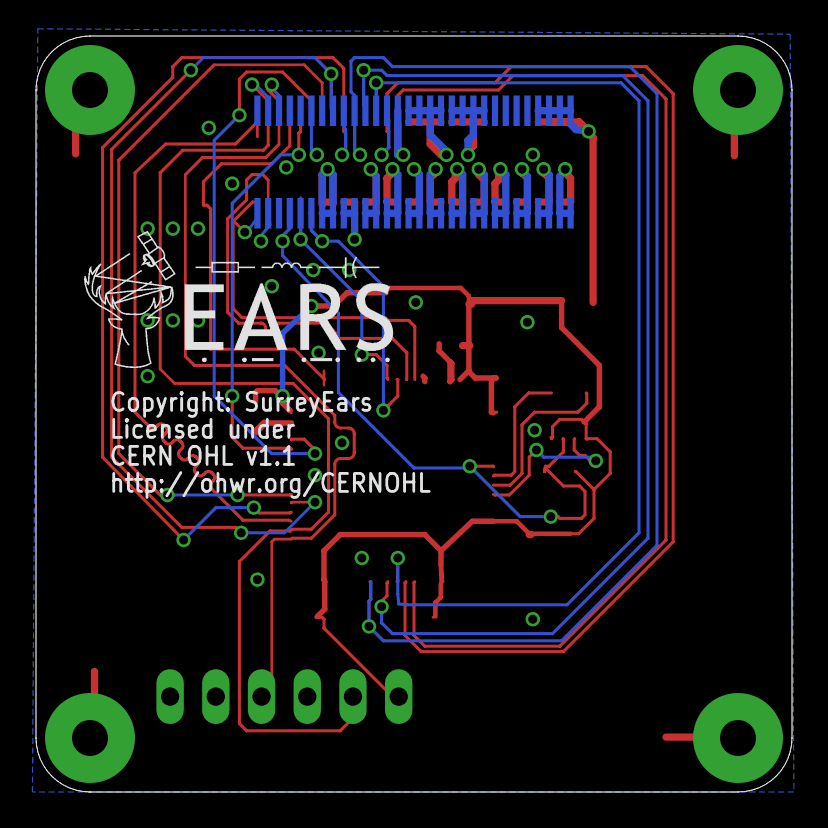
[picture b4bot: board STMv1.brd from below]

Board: 2 copper layers, 42.0 x 42.0 mm, 22 parts (2 on the bottom side), 40 nets.

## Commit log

2014-12-21 initial test commit
2014-12-21 Added template hardware files and a basic readme.
2014-12-21 Silly updates
2014-12-21 Added folder structure and fleshed out a bit.
2014-12-21 Fixed deletions
2014-12-22 Added artwork.
2014-12-22 renamed power board to eps. Added wiki link to readme
2015-06-14 Updating template, wip
2015-06-14 Finished updating to new PQ60 V1.1 standard
2015-06-15 Started Breakout Board. Still need to route some GPIO and SPI.
2015-06-15 completed routing breakout, need to tidy
2015-06-15 Finished tidying traces for now.
2015-06-16 Added images, changed description.
2015-06-20 fixed fx8c symbols
2015-06-20 added master changes
2015-06-20 Update readme.md
    Added license
2015-07-30 new file: hardware/boards/obc/OBC.brd new file: hardware/boards/obc/OBC.sch modified: hardware/boards/obc/readme.md
2015-07-30 new file: STM32F103/OBC.brd new file: STM32F103/STM31F103
2015-07-30 new file: STM32F103/2226.pdf new file: STM32F103/CD00161566.pdf new file: STM32F103/CD00164185.pdf new file: STM32F103/OBC.sch
2015-07-30 renamed: STM32F103/2226.pdf -> STM32F103/MAX63 datasheet.pdf renamed: STM32F103/CD00161566.pdf -> STM32F103/STM32F103RB datasheet.pdf renamed: STM32F103/CD00164185.pdf -> STM32F103/helpful.pdf
2015-07-30 deleted: obc/OBC.brd deleted: obc/OBC.sch renamed: obc/STM32F103/OBC.brd -> obc/STM32F103/STMv1.brd renamed: obc/STM32F103/OBC.sch -> obc/STM32F103/STMv1.sch modified: obc/readme.md new file: obc/rea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
2015-08-17 modified: STM32F103/STMv1.brd modified: STM32F103/STMv1.sch new file: STM32F103/ears.lbr
2015-09-29 Updated URLs
    Fixed URLs to use the new wiki sub-domain
2016-07-05 Added V2 breakout ready to order
2016-07-06 Finished breakout v2

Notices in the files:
hardware/boards/breakout/Breakout_v2.brd:
Copyright: SurreyEARS
Licensed under
CERN OHL v1.1
parts and their libraries:
SparkFun-Aesthetics: Licensing: Creative Commons ShareAlike 4.0 International - https://creativecommons.org/licenses/by-sa/4.0
